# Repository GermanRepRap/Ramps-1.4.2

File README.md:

Ramps-1.4.2
===========

forked from ultimachine/Ramps 1.4

The RAMPS 1.4.2 Change log

* Standard blade fuses instead of thermal fuses increasing the heat resilience.
 	
* Current carrying improved by increasing the thickness of the cooper at the PCB from 35 to 70 micro meters.

* Suppression caps added to each end-stop to avoid spurious signals.

* Added an additional connector to XY, E1 and E2 to connect a second stepper motor.

* Connector for external reset added.

* Labeled D8, D9,D10 with Heatbed, Extrude 1, Fan and Extruder 2.

Fully assembled available from German RepRap www.germanreprap.com

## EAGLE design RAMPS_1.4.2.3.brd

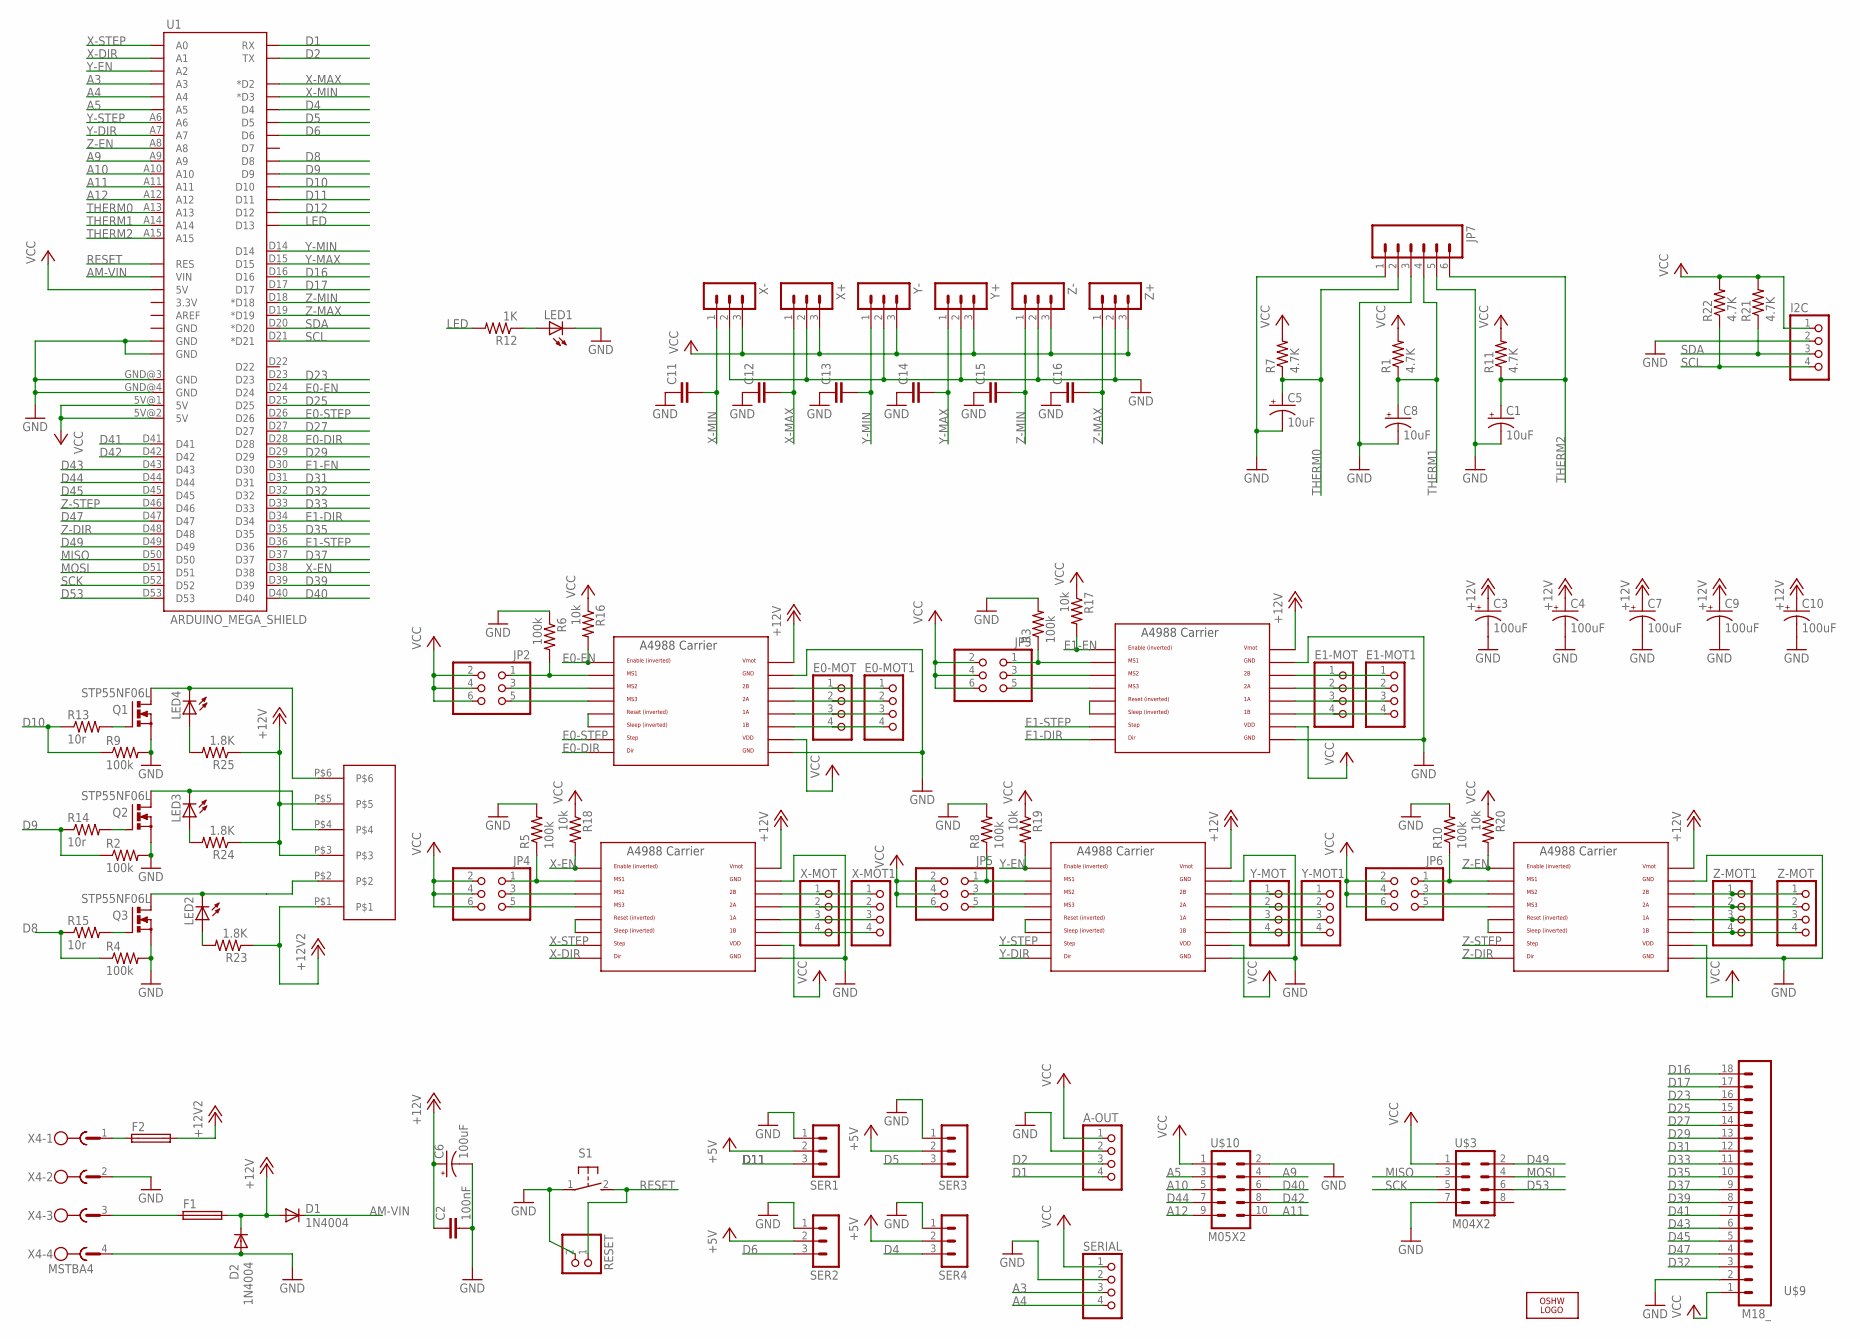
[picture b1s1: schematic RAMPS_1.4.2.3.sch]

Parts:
A-OUT: PINHD-1X4; 1X04
C1, C5, C8: 10uF; 153CLV-0405
C2: 100nF; C0805
C3, C4, C6, C7, C9, C10: 100uF; 153CLV-0605
C11, C12, C13, C14, C15, C16: C-EUC0805; C0805
D1, D2: 1N4004; DO41-10
E0-MOT, E0-MOT1, E1-MOT, E1-MOT1: PINHD-1X4; 1X04
F1, F2: FUSE_MCCQ-122
I2C: PINHD-1X4; 1X04
JP2, JP3, JP4, JP5, JP6: PINHD-2X3; 2X03
JP7: M06SIP; 1X06
LED1, LED2, LED3, LED4: LEDCHIP-LED0805; CHIP-LED0805
LOGO1: OSHW_LOGO_6MILX0100-NT; OSHW_6X100_NOTEXT
Q1, Q2, Q3: STP55NF06L; TO220BV
R1, R7, R11, R21, R22: 4.7K; R0805
R2, R3, R4, R5, R6, R8, R9, R10: 100k; R0805
R12: 1K; R0805
R13, R15: 10r; R0805
R14: 10r; M0805
R16, R17, R18, R19, R20: 10k; R0805
R23, R24, R25: 1.8K; R0805
RESET: PINHD-2
S1: 31-XX; B3F-31XX
SER1, SER2, SER3, SER4: 3PIN-HEADER
SERIAL: PINHD-1X4; 1X04
U1: ARDUINO_MEGA_SHIELD
U$2: 282837-6
U$3: M04X2; 2X4
U$4, U$5, U$6, U$7, U$8: A4988BREAKOUT
U$9: M18_; 1X18
U$10: M05X2; 2X5
X4: MSTBA4
X+: 3PIN-HEADER
X-: 3PIN-HEADER
X-MOT, X-MOT1: PINHD-1X4; 1X04
Y+: 3PIN-HEADER
Y-: 3PIN-HEADER
Y-MOT, Y-MOT1: PINHD-1X4; 1X04
Z+: 3PIN-HEADER
Z-: 3PIN-HEADER
Z-MOT, Z-MOT1: PINHD-1X4; 1X04

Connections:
+5V: SER1.2, SER2.2, SER3.2, SER4.2
+12V: C2.1, C3.+, C4.+, C6.+, C7.+, C9.+, C10.+, D1.A, D2.C, F1.2-1 (2), F1.2-2 (2), R24.1, R25.1, U$2.P$3, U$2.P$5, U$4.VMOT, U$5.VMOT, U$6.VMOT, U$7.VMOT, U$8.VMOT
+12V2: F2.2-1 (2), F2.2-2 (2), R23.1, U$2.P$1
A3: SERIAL.3, U1.A3
A4: SERIAL.4, U1.A4
A5: U1.A5, U$10.3
A9: U1.A9, U$10.4
A10: U1.A10, U$10.5
A11: U1.A11, U$10.10
A12: U1.A12, U$10.9
AM-VIN: D1.C, U1.VIN
D1: A-OUT.4, U1.RX
D2: A-OUT.3, U1.TX
D4: SER4.3, U1.D4
D5: SER3.3, U1.D5
D6: SER2.3, U1.D6
D8: R4.1, R15.1, U1.D8
D9: R2.1, R14.1, U1.D9
D10: R9.1, R13.1, U1.D10
D11: SER1.3, U1.D11
D12: U1.D12
D16: U1.D16, U$9.18
D17: U1.D17, U$9.17
D23: U1.D23, U$9.16
D25: U1.D25, U$9.15
D27: U1.D27, U$9.14
D29: U1.D29, U$9.13
D31: U1.D31, U$9.12
D32: U1.D32, U$9.3
D33: U1.D33, U$9.11
D35: U1.D35, U$9.10
D37: U1.D37, U$9.9
D39: U1.D39, U$9.8
D40: U1.D40, U$10.6
D41: U1.D41, U$9.7
D42: U1.D42, U$10.8
D43: U1.D43, U$9.6
D44: U1.D44, U$10.7
D45: U1.D45, U$9.5
D47: U1.D47, U$9.4
D49: U1.D49, U$3.2
D53: U1.D53, U$3.6
E0-DIR: U1.D28, U$4.DIR
E0-EN: R16.2, U1.D24, U$4.EN
E0-STEP: U1.D26, U$4.STEP
E1-DIR: U1.D34, U$5.DIR
E1-EN: R17.2, U1.D30, U$5.EN
E1-STEP: U1.D36, U$5.STEP
GND: A-OUT.2, C1.-, C2.2, C3.-, C4.-, C5.-, C6.-, C7.-, C8.-, C9.-, C10.-, C11.1, C12.1, C13.1, C14.1, C15.1, C16.1, D2.A, I2C.2, JP7.1, JP7.3, JP7.5, LED1.C, Q1.S, Q2.S, Q3.S, R2.2, R3.2, R4.2, R5.2, R6.1, R8.2, R9.2, R10.2, RESET.2, S1.1, SER1.1, SER2.1, SER3.1, SER4.1, SERIAL.2, U1.GND@0 (GND), U1.GND@1 (GND), U1.GND@3 (GND), U1.GND@4 (GND), U$3.7, U$4.GND, U$4.GND@0 (GND), U$5.GND, U$5.GND@0 (GND), U$6.GND, U$6.GND@0 (GND), U$7.GND, U$7.GND@0 (GND), U$8.GND, U$8.GND@0 (GND), U$9.2, U$10.2, X4.2, X4.4, X+.2, X-.2, Y+.2, Y-.2, Z+.2, Z-.2
LED: R12.2, U1.D13
MISO: U1.D50, U$3.3
MOSI: U1.D51, U$3.4
unnamed: LED3.C, Q2.D, U$2.P$4
unnamed: E0-MOT.1, E0-MOT1.1, U$4.2B
unnamed: E0-MOT.2, E0-MOT1.2, U$4.2A
unnamed: JP2.1, R6.2, U$4.MS1
unnamed: JP2.5, U$4.MS3
unnamed: LED4.C, Q1.D, U$2.P$6
unnamed: U$4.RST, U$4.SLP (SLEEP)
unnamed: JP2.3, U$4.MS2
unnamed: E0-MOT.3, E0-MOT1.3, U$4.1A
unnamed: E0-MOT.4, E0-MOT1.4, U$4.1B
unnamed: E1-MOT.1, E1-MOT1.1, U$5.2B
unnamed: E1-MOT.2, E1-MOT1.2, U$5.2A
unnamed: JP4.1, R5.1, U$6.MS1
unnamed: JP4.3, U$6.MS2
unnamed: E1-MOT.3, E1-MOT1.3, U$5.1A
unnamed: JP5.3, U$7.MS2
unnamed: E1-MOT.4, E1-MOT1.4, U$5.1B
unnamed: JP4.5, U$6.MS3
unnamed: U$6.RST, U$6.SLP (SLEEP)
unnamed: U$6.2B, X-MOT.1, X-MOT1.1
unnamed: U$6.2A, X-MOT.2, X-MOT1.2
unnamed: U$7.RST, U$7.SLP (SLEEP)
unnamed: U$5.RST, U$5.SLP (SLEEP)
unnamed: JP3.1, R3.1, U$5.MS1
unnamed: U$6.1A, X-MOT.3, X-MOT1.3
unnamed: U$6.1B, X-MOT.4, X-MOT1.4
unnamed: U$7.2B, Y-MOT.1, Y-MOT1.1
unnamed: U$7.2A, Y-MOT.2, Y-MOT1.2
unnamed: U$7.1A, Y-MOT.3, Y-MOT1.3
unnamed: JP5.5, U$7.MS3
unnamed: LED2.A, R23.2
unnamed: JP5.1, R8.1, U$7.MS1
unnamed: JP3.5, U$5.MS3
unnamed: JP3.3, U$5.MS2
unnamed: U$7.1B, Y-MOT.4, Y-MOT1.4
unnamed: JP6.3, U$8.MS2
unnamed: U$8.RST, U$8.SLP (SLEEP)
unnamed: JP6.5, U$8.MS3
unnamed: JP6.1, R10.1, U$8.MS1
unnamed: U$8.2B, Z-MOT.1, Z-MOT1.1
unnamed: U$8.2A, Z-MOT.2, Z-MOT1.2
unnamed: U$8.1A, Z-MOT.3, Z-MOT1.3
unnamed: U$8.1B, Z-MOT.4, Z-MOT1.4
unnamed: LED3.A, R24.2
unnamed: LED1.A, R12.1
unnamed: Q2.G, R14.2
unnamed: Q1.G, R13.2
unnamed: Q3.G, R15.2
unnamed: LED4.A, R25.2
unnamed: LED2.C, Q3.D, U$2.P$2
unnamed: F2.1-1 (1), F2.1-2 (1), X4.1
unnamed: F1.1-1 (1), F1.1-2 (1), X4.3
RESET: RESET.1, S1.2 (S), U1.RES
SCK: U1.D52, U$3.5
SCL: I2C.4, R22.1, U1.D21 (*D21)
SDA: I2C.3, R21.1, U1.D20 (*D20)
THERM0: C5.+, JP7.2, R7.1, U1.A13
THERM1: C8.+, JP7.4, R1.1, U1.A14
THERM2: C1.+, JP7.6, R11.1, U1.A15
VCC: A-OUT.1, I2C.1, JP2.2, JP2.4, JP2.6, JP3.2, JP3.4, JP3.6, JP4.2, JP4.4, JP4.6, JP5.2, JP5.4, JP5.6, JP6.2, JP6.4, JP6.6, R1.2, R7.2, R11.2, R16.1, R17.1, R18.1, R19.1, R20.1, R21.2, R22.2, SERIAL.1, U1.5V@0 (5V), U1.5V@1 (5V), U1.5V@2 (5V), U$3.1, U$4.VDD, U$5.VDD, U$6.VDD, U$7.VDD, U$8.VDD, U$9.1, U$10.1, X+.3, X-.3, Y+.3, Y-.3, Z+.3, Z-.3
X-DIR: U1.A1, U$6.DIR
X-EN: R18.2, U1.D38, U$6.EN
X-MAX: C12.2, U1.D2 (*D2), X+.1
X-MIN: C11.2, U1.D3 (*D3), X-.1
X-STEP: U1.A0, U$6.STEP
Y-DIR: U1.A7, U$7.DIR
Y-EN: R19.2, U1.A2, U$7.EN
Y-MAX: C14.2, U1.D15, Y+.1
Y-MIN: C13.2, U1.D14, Y-.1
Y-STEP: U1.A6, U$7.STEP
Z-DIR: U1.D48, U$8.DIR
Z-EN: R20.2, U1.A8, U$8.EN
Z-MAX: C16.2, U1.D19 (*D19), Z+.1
Z-MIN: C15.2, U1.D18 (*D18), Z-.1
Z-STEP: U1.D46, U$8.STEP

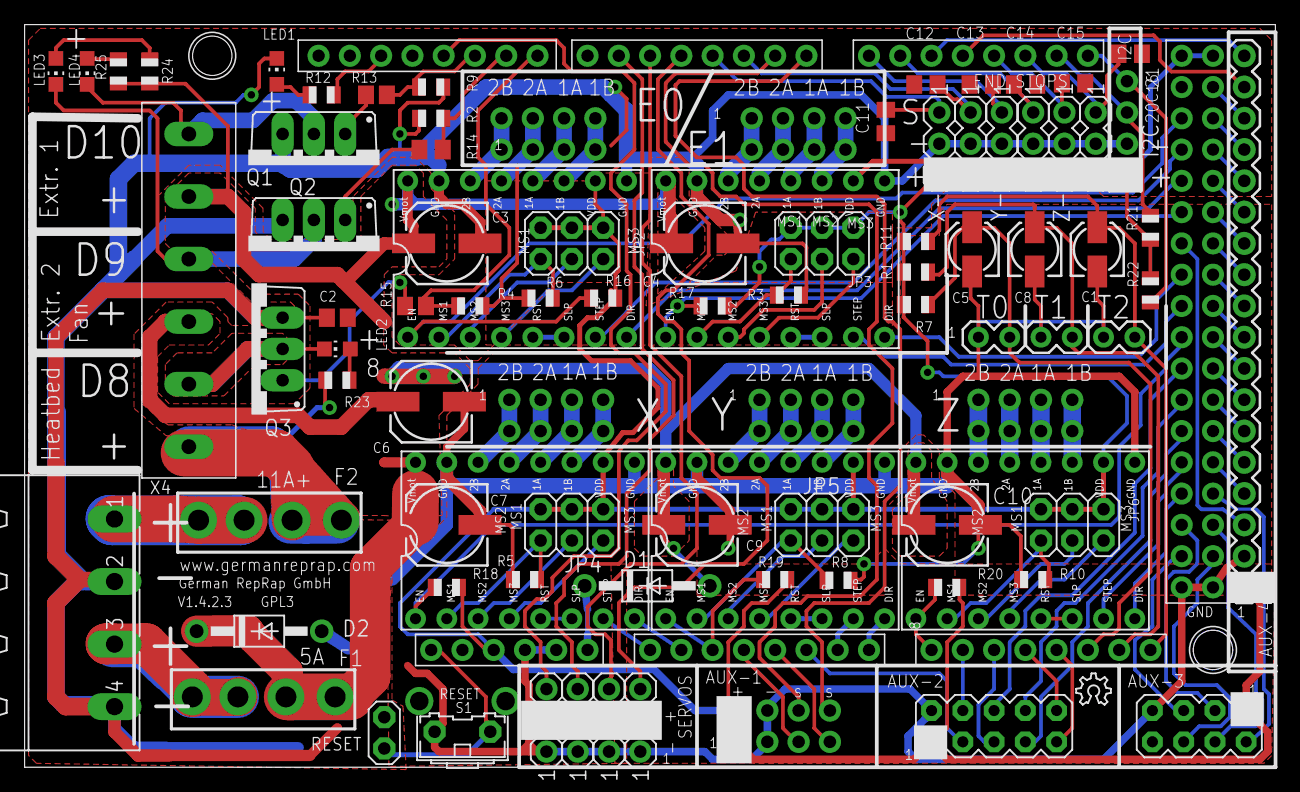
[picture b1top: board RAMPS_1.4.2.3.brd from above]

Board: 2 copper layers, 101.6 x 60.3 mm, 95 parts (0 on the bottom side), 126 nets.

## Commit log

2013-11-28 New Readme
2014-07-17 Gerber Files
    Generated by SeeedStudio 2-Layer Gerber Generator
2014-07-18 Pdf for printing Added

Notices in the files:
RAMPS_1.4.2.3.brd:
GPL3
GPL v3
Copyright 2011 Johnny Russell - UltiMachine
